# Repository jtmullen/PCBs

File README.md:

View this project on [CADLAB.io](https://cadlab.io/project/23086). 

Hello!

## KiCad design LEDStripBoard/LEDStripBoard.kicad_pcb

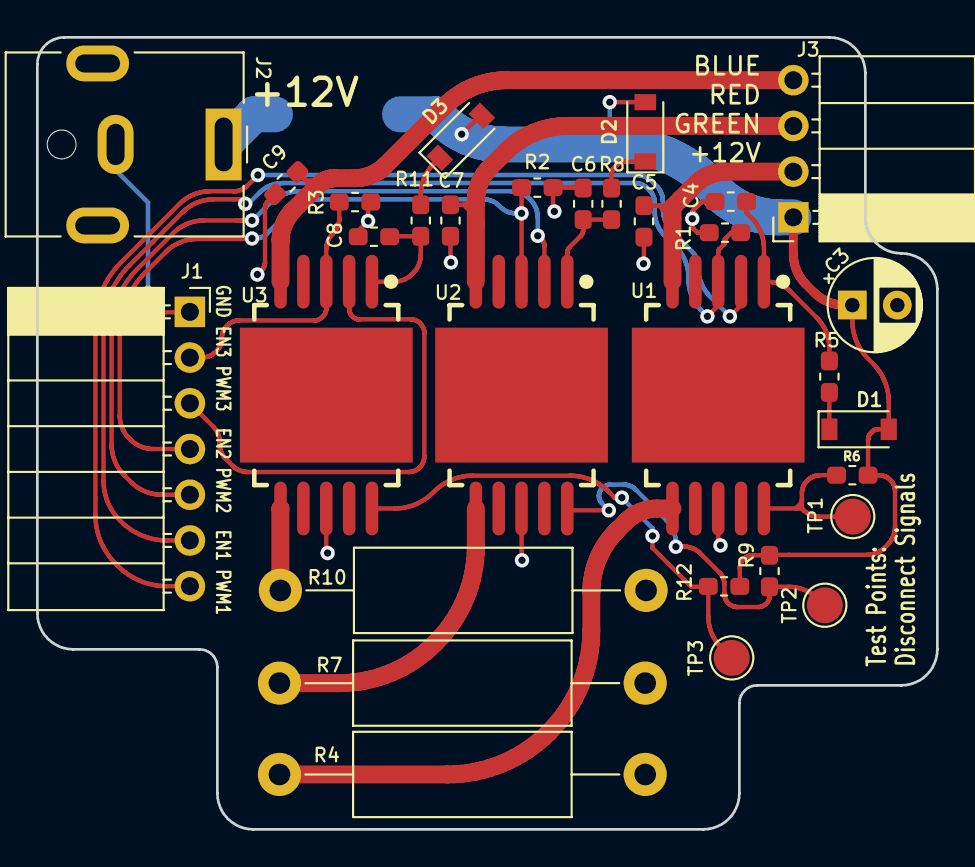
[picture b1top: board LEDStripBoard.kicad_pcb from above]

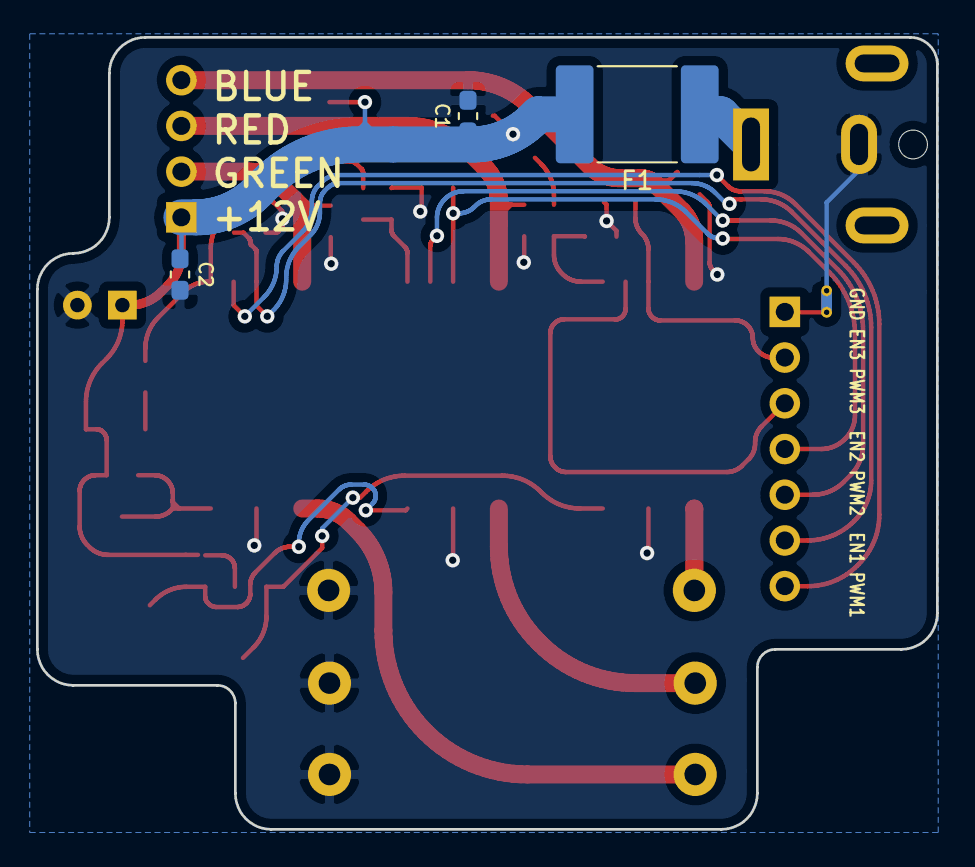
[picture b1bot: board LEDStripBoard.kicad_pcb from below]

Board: 2 copper layers, 50.0 x 44.0 mm, 35 parts (4 on the bottom side), 25 nets.

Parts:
C1, C4, C6, C8: 0.1uF; C_0603_1608Metric_Pad1.05x0.95mm_HandSolder
C2: 1uF; C_0603_1608Metric_Pad1.05x0.95mm_HandSolder
C3: CP1; CP_Radial_D5.0mm_P2.50mm
C5, C7, C9: 0.47uF; C_0603_1608Metric_Pad1.05x0.95mm_HandSolder
D1, D2, D3: BAT46; D_SOD-123
F1: 3A; Fuse_2920_7451Metric_Pad2.10x5.45mm_HandSolder
J1: Conn_01x07; PinSocket_1x07_P2.54mm_Horizontal
J2: Barrel_Jack; BarrelJack_CUI_PJ-063AH_Horizontal
J3: Conn_01x04; PinSocket_1x04_P2.54mm_Horizontal
NT1: Net-Tie_2; NetTie-2_THT_Pad0.3mm
R1, R2, R3, R6, R9, R12: 1k; R_0603_1608Metric_Pad1.05x0.95mm_HandSolder
R4, R7, R10: 0.1; R_Axial_DIN0414_L11.9mm_D4.5mm_P20.32mm_Horizontal
R5, R8, R11: 100; R_0603_1608Metric_Pad1.05x0.95mm_HandSolder
TP1, TP2, TP3: TestPoint; TestPoint_Pad_D2.0mm
U1, U2, U3: STCS2; POWERSO-10

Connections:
+12V: C1.1, C2.1, C3.1, D1.2, D2.2, D3.2, F1.2, J3.1, R6.1, R9.1, R12.1
/Driver Blue/DRAIN: C9.1, J3.4, U3.5
/Driver Blue/Enable: J1.2, R3.1, U3.3
/Driver Blue/PWM: J1.3, U3.2
/Driver Green/DRAIN: C7.1, J3.3, U2.5
/Driver Green/Enable: J1.4, R2.1, U2.3
/Driver Green/PWM: J1.5, U2.2
/Driver Red/DRAIN: C5.1, J3.2, U1.5
/Driver Red/Enable: J1.6, R1.1, U1.3
/Driver Red/PWM: J1.7, U1.2
GND: C1.2, C2.2, C3.2, C4.2, C5.2, C6.2, C7.2, C8.2, C9.2, J2.2, NT1.1, R1.2, R2.2, R3.2, R4.2, R7.2, R10.2, U1.8, U2.8, U3.8
unnamed: C4.1, R5.2, U1.1
unnamed: C6.1, R8.2, U2.1
unnamed: C8.1, R11.2, U3.1
unnamed: D1.1, R5.1
unnamed: D2.1, R8.1
unnamed: D3.1, R11.1
unnamed: F1.1, J2.1
unnamed: J1.1, NT1.2
unnamed: R4.1, U1.6
unnamed: R6.2, TP1.1, U1.10
unnamed: R7.1, U2.6
unnamed: R9.2, TP2.1, U2.10
unnamed: R10.1, U3.6
unnamed: R12.2, TP3.1, U3.10

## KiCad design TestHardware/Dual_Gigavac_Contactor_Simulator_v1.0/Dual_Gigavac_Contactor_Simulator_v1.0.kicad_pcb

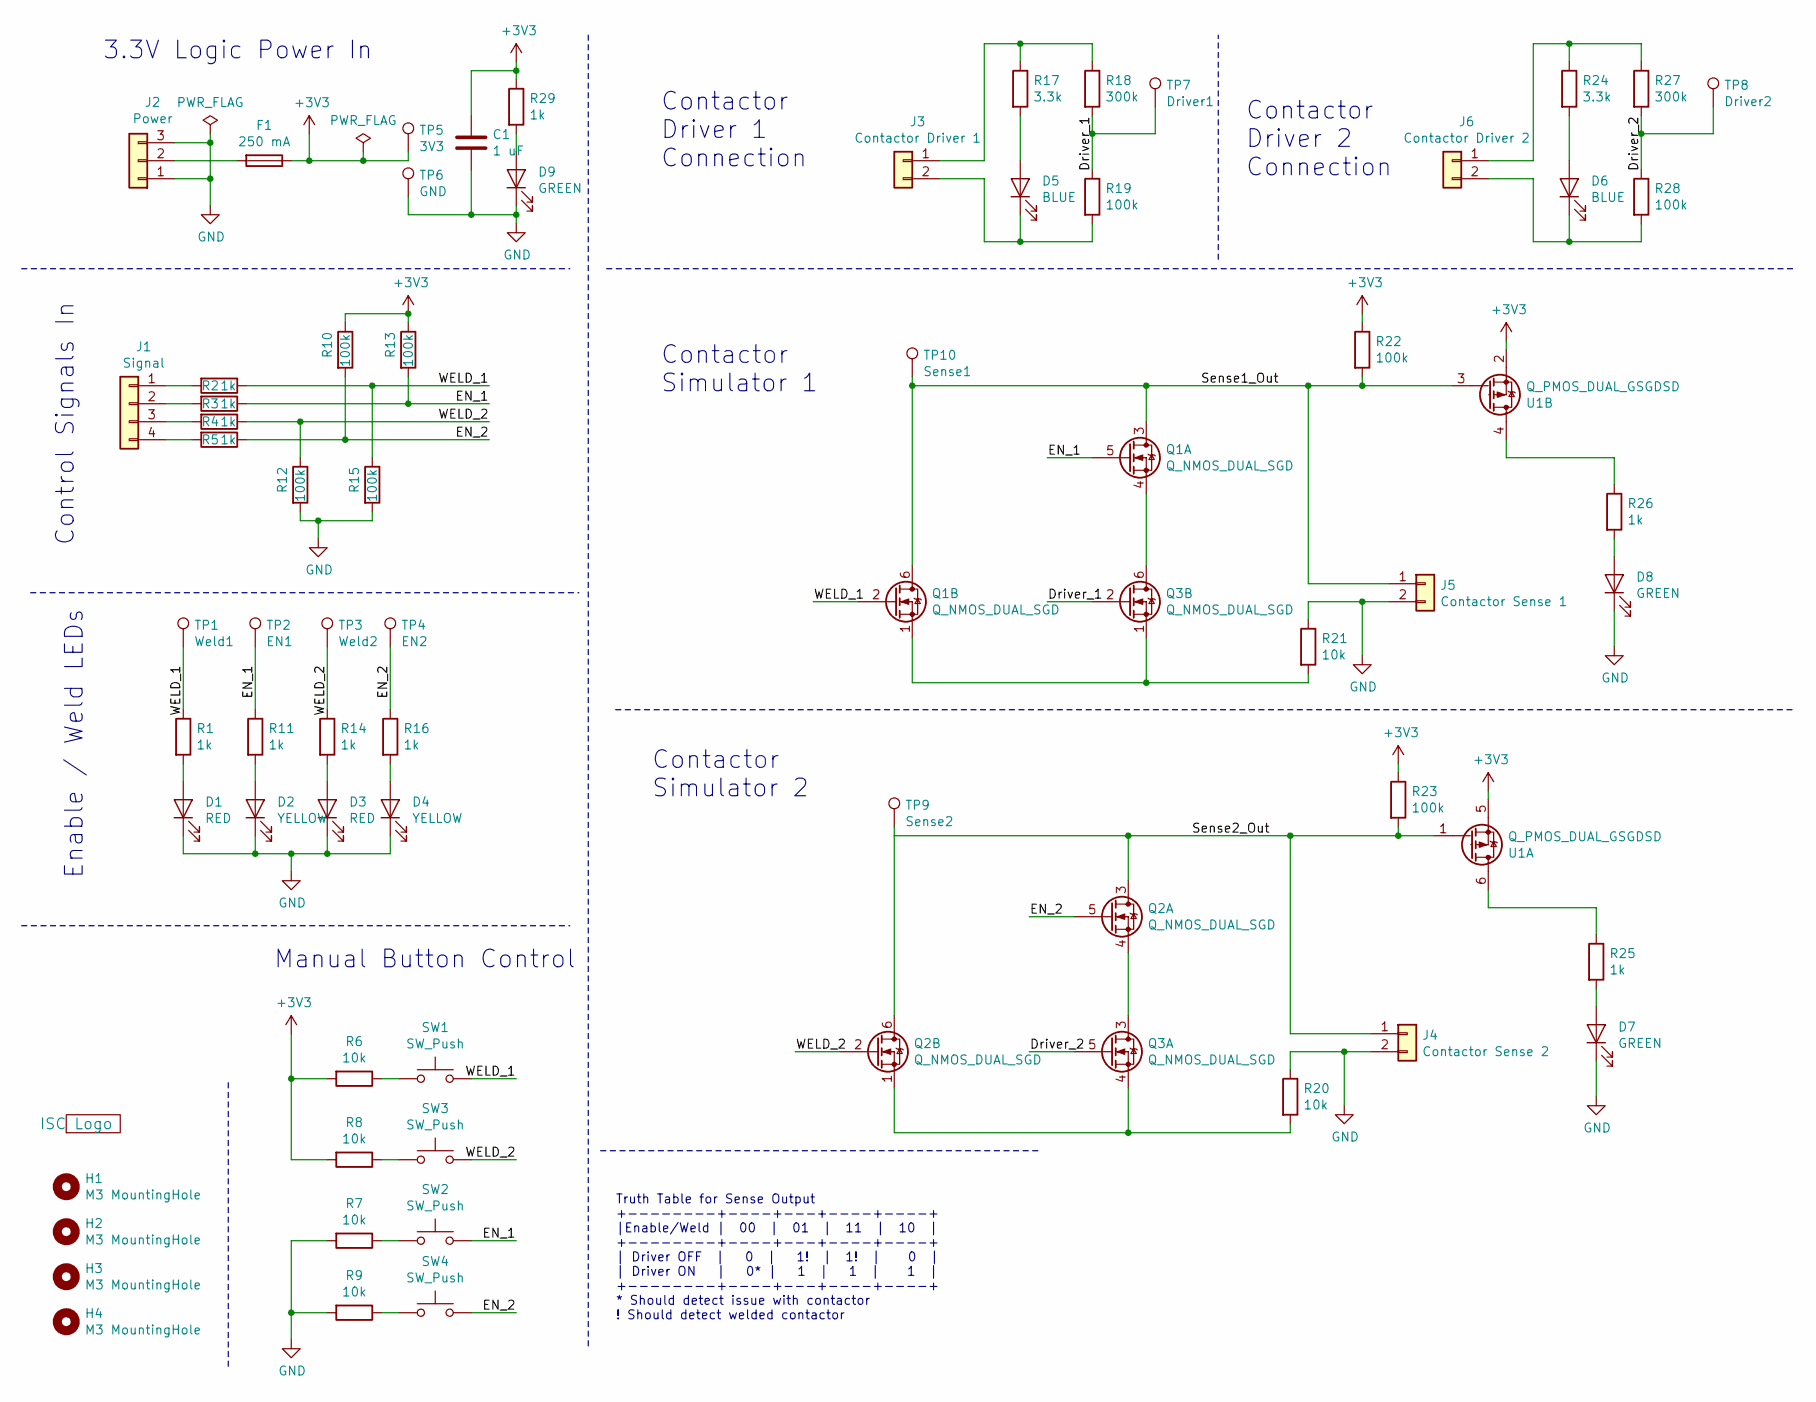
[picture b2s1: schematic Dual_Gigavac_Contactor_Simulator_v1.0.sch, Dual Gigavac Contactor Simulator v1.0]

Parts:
C1: 1 uF; C_0603_1608Metric_Pad1.05x0.95mm_HandSolder; MPN CAP CER 1UF 10V X5R 0603
D1, D3: RED; LED_0603_1608Metric_Pad1.05x0.95mm_HandSolder; MPN LED RED CLEAR 0603 SMD
D2, D4: YELLOW; LED_0603_1608Metric_Pad1.05x0.95mm_HandSolder; MPN LED YELLOW CLEAR 0603 SMD
D5, D6: BLUE; LED_0603_1608Metric_Pad1.05x0.95mm_HandSolder; MPN LED BLUE CLEAR 0603 SMD
D7, D8, D9: GREEN; LED_0603_1608Metric_Pad1.05x0.95mm_HandSolder; MPN LED GREEN CLEAR 0603 SMD
F1: 250 mA; Fuse_0603_1608Metric_Pad1.05x0.95mm_HandSolder; MPN FUSE BOARD MNT 250MA 32VDC 0603
H1, H2, H3, H4: M3 MountingHole; MountingHole_3.2mm_M3
J1: Signal; Molex_KK-254_AE-6410-04A_1x04_P2.54mm_Vertical; MPN 22-27-2041
J2: Power; Molex_KK-254_AE-6410-03A_1x03_P2.54mm_Vertical; MPN 22-27-2031
J3: Contactor Driver 1; Molex_KK-254_AE-6410-02A_1x02_P2.54mm_Vertical; MPN 22-27-2021
J4: Contactor Sense 2; Molex_KK-254_AE-6410-02A_1x02_P2.54mm_Vertical; MPN 22-27-2021
J5: Contactor Sense 1; Molex_KK-254_AE-6410-02A_1x02_P2.54mm_Vertical; MPN 22-27-2021
J6: Contactor Driver 2; Molex_KK-254_AE-6410-02A_1x02_P2.54mm_Vertical; MPN 22-27-2021
MK1: ISC Logo; ISC_BLogo
Q1, Q2, Q3: Q_NMOS_DUAL_SGD; SOT-363_SC-70-6; MPN 2N7002DW
R1, R2, R3, R4, R5, R11, R14, R16, R25, R26, R29: 1k; R_0603_1608Metric_Pad1.05x0.95mm_HandSolder; MPN RES SMD 1K OHM 5% 1/10W 0603
R6, R7, R8, R9: 10k; R_0603_1608Metric_Pad1.05x0.95mm_HandSolder; MPN RES SMD 10K OHM 5% 1/10W 0603
R10, R12, R13, R15, R19, R22, R23, R28: 100k; R_0603_1608Metric_Pad1.05x0.95mm_HandSolder; MPN RES SMD 100K OHM 5% 1/10W 0603
R17, R24: 3.3k; R_0603_1608Metric_Pad1.05x0.95mm_HandSolder; MPN RES SMD 3.3K OHM 5% 1/10W 0603
R18, R27: 300k; R_0603_1608Metric_Pad1.05x0.95mm_HandSolder; MPN RES SMD 300K OHM 5% 1/10W 0603
R20, R21: 10k; R_0603_1608Metric_Pad1.05x0.95mm_HandSolder; MPN RES SMD 10K OHM 5% 1/4W 0603
SW1, SW2, SW3, SW4: SW_Push; Button_223AM; MPN 223AMVAAR
TP1: Weld1; TestPoint_Pad_D1.5mm
TP2: EN1; TestPoint_Pad_D1.5mm
TP3: Weld2; TestPoint_Pad_D1.5mm
TP4: EN2; TestPoint_Pad_D1.5mm
TP5: 3V3; TestPoint_Pad_D1.5mm
TP6: GND; TestPoint_Pad_D1.5mm
TP7: Driver1; TestPoint_Pad_D1.5mm
TP8: Driver2; TestPoint_Pad_D1.5mm
TP9: Sense2; TestPoint_Pad_D1.5mm
TP10: Sense1; TestPoint_Pad_D1.5mm
U1: Q_PMOS_DUAL_GSGDSD; SuperSOT-6; MPN NDC7003P

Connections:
+3V3: C1.1, F1.1, R6.2, R8.2, R10.1, R13.1, R22.1, R23.1, R29.1, TP5.1, U1.2 (Source), U1.5 (Source)
/Driver_1: Q3.2 (G), R18.2, R19.1, TP7.1
/Driver_2: Q3.5 (G), R27.2, R28.1, TP8.1
/EN_1: Q1.5 (G), R3.1, R11.1, R13.2, SW2.2, TP2.1
/EN_2: Q2.5 (G), R5.1, R10.2, R16.1, SW4.2, TP4.1
/Sense1_Out: J5.1, Q1.3 (D), Q1.6 (D), R22.2, TP10.1, U1.3 (Gate)
/Sense2_Out: J4.1, Q2.3 (D), Q2.6 (D), R23.2, TP9.1, U1.1 (Gate)
/WELD_1: Q1.2 (G), R1.1, R2.1, R15.1, SW1.2, TP1.1
/WELD_2: Q2.2 (G), R4.1, R12.1, R14.1, SW3.2, TP3.1
GND: C1.2, D1.1 (K), D2.1 (K), D3.1 (K), D4.1 (K), D7.1 (K), D8.1 (K), D9.1 (K), J2.1, J2.3, J4.2, J5.2, R7.2, R9.2, R12.2, R15.2, R20.1, R21.1, TP6.1
unnamed: D1.2 (A), R1.2
unnamed: D2.2 (A), R11.2
unnamed: D3.2 (A), R14.2
unnamed: D4.2 (A), R16.2
unnamed: D5.1 (K), J3.2, R19.2
unnamed: D5.2 (A), R17.2
unnamed: D6.1 (K), J6.2, R28.2
unnamed: D6.2 (A), R24.2
unnamed: D7.2 (A), R25.2
unnamed: D8.2 (A), R26.2
unnamed: D9.2 (A), R29.2
unnamed: F1.2, J2.2
unnamed: J1.1, R2.2
unnamed: J1.2, R3.2
unnamed: J1.3, R4.2
unnamed: J1.4, R5.2
unnamed: J3.1, R17.1, R18.1
unnamed: J6.1, R24.1, R27.1
unnamed: Q1.1 (S), Q3.1 (S), R21.2
unnamed: Q1.4 (S), Q3.6 (D)
unnamed: Q2.1 (S), Q3.4 (S), R20.2
unnamed: Q2.4 (S), Q3.3 (D)
unnamed: R6.1, SW1.1
unnamed: R7.1, SW2.1
unnamed: R8.1, SW3.1
unnamed: R9.1, SW4.1
unnamed: R25.1, U1.6 (Drain)
unnamed: R26.1, U1.4 (Drain)

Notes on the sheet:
3.3V Logic Power In
Control Signals In
Enable / Weld LEDs
Manual Button Control
Truth Table for Sense Output +--------+----+---+----+----+ |Enable/Weld | 00 | 01 | 11 | 10 | +--------+----+---+----+----+ | Driver OFF | 0 | 1! | 1! | 0 | | Driver ON | 0* | 1 | 1 | 1 | +--------+----+---+----+----+ * Should detect issue with contactor ! Should detect welded contactor
Contactor Driver 1 Connection
Contactor Driver 2 Connection
Contactor Simulator 1
Contactor Simulator 2

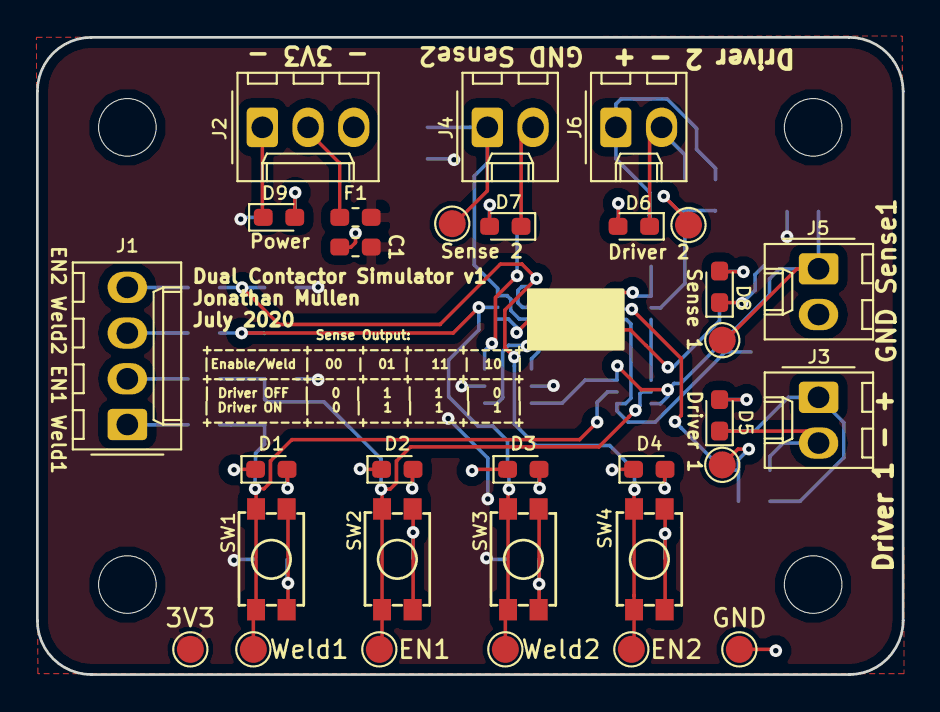
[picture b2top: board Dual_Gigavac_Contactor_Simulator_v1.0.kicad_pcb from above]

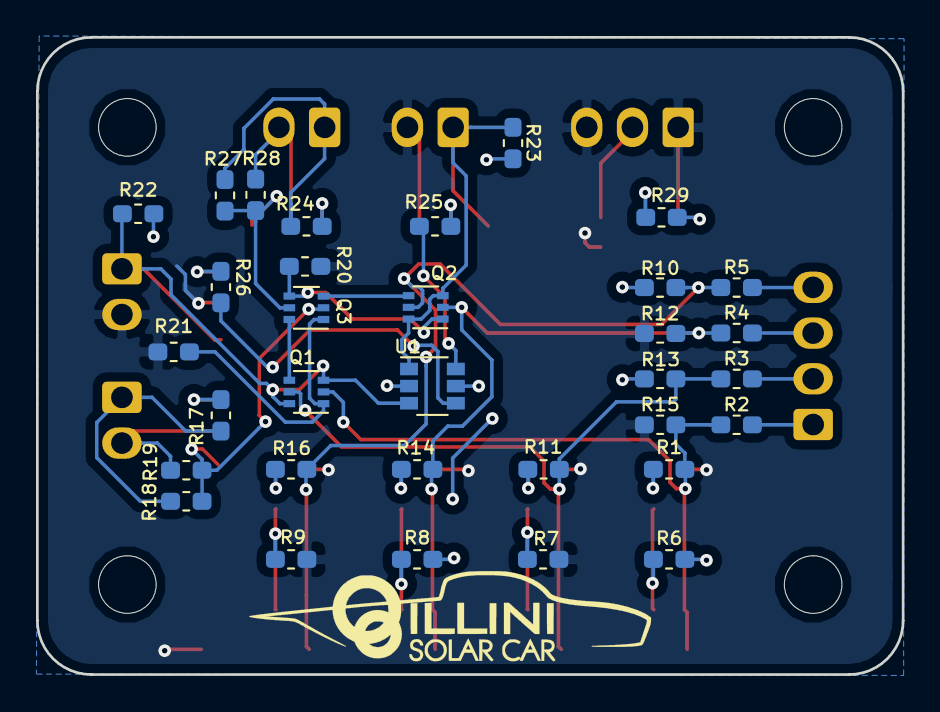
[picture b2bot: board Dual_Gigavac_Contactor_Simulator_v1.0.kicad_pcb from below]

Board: 2 copper layers, 48.1 x 35.4 mm, 69 parts (34 on the bottom side), 38 nets.

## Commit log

2020-07-09 Backlink to CADLAB.io has been added.
2020-07-09 Board from ISC Repo
2020-07-09 Remove unused sheet
2020-07-09 Minor tweaks
2020-07-27 Fix U1A & B Orientation
2020-10-21 Updates from other repo
2020-12-22 CJ Board
2020-12-22 Add vcc Diode
